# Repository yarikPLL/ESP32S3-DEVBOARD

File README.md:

# ESP32-S3 DevBoard (Recruitment Task)

This project is a custom development board based on the ESP32-S3, created as part of a recruitment task.  
Although the task was intended for candidates, I also completed it myself as a reference and benchmark solution.

## Overview

The board is based on the **ESP32-S3-WROOM-1** module and follows the general idea of standard development boards.

The pinout is **fully compatible with the original ESP32-S3 dev boards**, so it can be used as a drop-in replacement in typical setups.

## Features

- ESP32-S3-WROOM-1 module
- 2x USB Type-C connectors for power, programming, and communication OTG
- USB-to-UART converter based on **CP2102N** with auto-programming circuit
- IMU sensor (BMI270) connected via **I2C**
- 2x user LED indicators (0403) and UART led indicators
- Reset, boot and 2 users buttons
- DIP switch for flexible configuration

## Configuration (DIP Switch)

The board includes a DIP switch that allows:

- Enabling/disabling the USB-to-TTL converter  
- Enabling/disabling the IMU sensor  
- Powering off the ESP32 (useful when using the board purely as a USB-UART converter)

## IMU

An IMU sensor (BMI series) has been added and connected via the I2C interface.  
This allows easy integration of motion sensing features in future projects.

## USB to UART

The board includes a **CP2102N** USB-to-TTL converter with an auto-programming circuit, enabling:

- Firmware flashing
- Serial communication
- Seamless development workflow

## PCB Layout

Below are renders and layout views of the board:

### Layout

### 3D Views

#### Top View

#### Bottom View

#### Isometric Top

#### Isometric Bottom

## Notes

This project was created as part of a recruitment process to evaluate practical hardware design skills, including:

- schematic design
- PCB layout
- manufacturability
- documentation

## License

This project is licensed under the GNU Lesser General Public License v2.1 (LGPL-2.1).

You are free to use, modify, and distribute this project under the terms of this license.

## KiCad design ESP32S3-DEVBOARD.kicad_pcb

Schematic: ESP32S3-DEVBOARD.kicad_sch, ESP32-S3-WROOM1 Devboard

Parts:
C1, C2, C4, C5, C7, C9, C11, C12, C13: 100n; C_0402_1005Metric; MFR Part # CL05B104KO5NNNC; LCSC C1525
C3, C6, C8: 10u_{ 20%}; C_0603_1608Metric; MFR Part # CL10A106MA8NRNC; LCSC C96446
C10, C15, C16: 100n; C_0402_1005Metric; MFR Part # CL05B104KO5NNNC; LCSC C1525; not fitted
C14: 10u_{ 20%}; C_0603_1608Metric; LCSC C96446; not fitted
D1, D3: RED; LED_0402_1005Metric; MFR Part # 16-213SDRC/S530-A3/TR8; LCSC C71911
D2, D4: GREEN; LED_0402_1005Metric; MFR Part # 16-213/GHC-YR1S1/3T; LCSC C74338
J1, J2: PinHeader_1x22_P2.54mm_Vertical; PinHeader_1x22_P2.54mm_Vertical_FLIPPED
J3, J4: G-Switch_GT-USB-7010ASV; USB_C_Receptacle_G-Switch_GT-USB-7010ASV; LCSC C2988369
Q1, Q2: BC817-40,215; LCSC C52801
R1, R5: 0R; R_0402_1005Metric; MFR Part # RC0402FR-070RL; LCSC C106231
R2, R3, R4, R8, R13, R14, R15: 10k; R_0402_1005Metric; MFR Part # RC0402FR-0710KL; LCSC C60490
R6, R7, R16, R17: 5.1k; R_0402_1005Metric; MFR Part # 0402WGF5101TCE; LCSC C25905
R9: 22.1k; R_0402_1005Metric; MFR Part # FRC0402F2212TS; LCSC C2929993
R10: 47.5k; R_0402_1005Metric; MFR Part # 0402WGF4752TCE; LCSC C25896
R11, R12, R20, R21: 1k; R_0402_1005Metric; MFR Part # 0402WGF1001TCE; LCSC C11702
SW1, SW2, SW3, SW4: TS-1088-AR02016; MFR Part # TS-1088-AR02016; LCSC C720477
SW5: SHOU_HAN_1.27-8P_TPPT; SHOU_HAN_1.27-8P_TTPT; MFR Part # 1.27-8P TPPT; LCSC C6386921
U1: AMS1117-3.3; LCSC C6186
U2: ESP32-S3-WROOM-1; LCSC C2913205
U3, U6: USBLC6-2P6; SOT-666; MFR Part # USBLC6-2P6; LCSC C2827693
U4: CP2102N-A02-GQFN28R; LCSC C964632
U5: BMI270; MFR Part # BMI270; LCSC C2836813

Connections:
+3.3V: C1.2, C2.2, C5.1, C6.1, C11.2, C12.1, C13.1, C16.1, J1.1, J1.2, R3.1, R8.1, R11.1, R12.1, R13.1, R14.1, SW5.11, U1.2 (VO), U2.2 (3V3), U4.6 (VDD), U5.5 (VDDIO), U5.8 (VDD)
+5V: C3.1, C4.1, C8.1, C9.1, C10.2, C14.1, C15.1, J1.21, J3.A4 (VBUS), J3.A9 (VBUS), J3.B4 (VBUS), J3.B9 (VBUS), J4.A4 (VBUS), J4.A9 (VBUS), J4.B4 (VBUS), J4.B9 (VBUS), R9.1, U1.3 (VI), U3.5 (VBUS), U6.5 (VBUS)
/CSB_U5: R15.1, SW5.6, U5.12 (CSB)
/DTR: Q2.3 (C), R2.2, U4.28 (~DTR)
/EN: C7.2, J1.3, R1.2, R3.2, SW1.2, SW5.1, U2.3 (EN)
/GPIO0: J2.14, R5.2, SW2.2, U2.27 (IO0)
/GPIO1: J2.4, U2.39 (IO1)
/GPIO2: J2.5, U2.38 (IO2)
/GPIO3: J1.13, U2.15 (IO3)
/GPIO4: J1.4, U2.4 (IO4)
/GPIO5: J1.5, U2.5 (IO5)
/GPIO6: J1.6, U2.6 (IO6)
/GPIO7: J1.7, U2.7 (IO7)
/GPIO8: J1.12, U2.12 (IO8)
/GPIO9: J1.15, U2.17 (IO9)
/GPIO10: J1.16, U2.18 (IO10)
/GPIO11: J1.17, U2.19 (IO11)
/GPIO12: J1.18, U2.20 (IO12)
/GPIO13: J1.19, R20.1, U2.21 (IO13)
/GPIO14: J1.20, R21.1, U2.22 (IO14)
/GPIO15: J1.8, SW3.1, U2.8 (IO15)
/GPIO16: J1.9, SW4.1, U2.9 (IO16)
/GPIO17: J1.10, U2.10 (IO17)
/GPIO18: J1.11, U2.11 (IO18)
/GPIO21: J2.18, SW5.12, U2.23 (IO21)
/GPIO35: J2.13, SW5.15, U2.28 (IO35)
/GPIO36: J2.12, U2.29 (IO36)
/GPIO37: J2.11, U2.30 (IO37)
/GPIO38: J2.10, U2.31 (IO38)
/GPIO39: J2.9, U2.32 (IO39)
/GPIO40: J2.8, U2.33 (IO40)
/GPIO41: J2.7, U2.34 (IO41)
/GPIO42: J2.6, U2.35 (IO42)
/GPIO43: J2.2, SW5.9, U2.37 (TXD0)
/GPIO44: J2.3, SW5.10, U2.36 (RXD0)
/GPIO45: J2.15, U2.26 (IO45)
/GPIO46: J1.14, U2.16 (IO46)
/GPIO47: J2.17, SW5.13, U2.24 (IO47)
/GPIO48: J2.16, SW5.14, U2.25 (IO48)
/INT1: SW5.2, U5.4 (INT1)
/INT2: SW5.5, U5.9 (INT2)
/I^{2}C_SCL: R14.2, SW5.4, U5.13 (SCX)
/I^{2}C_SDA: R13.2, SW5.3, U5.14 (SDX)
/RST: R8.2, U4.9 (~RST)
/RTS: Q1.2 (E), R4.2, U4.24 (~RTS)
/RX_LED: D2.1 (K), U4.18 (~RXT/GPIO.1)
/TX_LED: D1.1 (K), U4.19 (~TXT/GPIO.0)
/U2_RX: SW5.8, U4.25 (RXD)
/U2_TX: SW5.7, U4.26 (TXD)
/U2_VBUS: R9.2, R10.1, U4.8 (VBUS)
/USB0_D+: U3.6 (I/O1), U4.4 (D+)
/USB0_D-: U3.4 (I/O2), U4.5 (D-)
/USB0_T_D+: J3.A6 (D+), J3.B6 (D+), U3.1 (I/O1)
/USB0_T_D-: J3.A7 (D-), J3.B7 (D-), U3.3 (I/O2)
/USB1_D+: J2.19, U2.14 (USB_D+), U6.4 (I/O2)
/USB1_D-: J2.20, U2.13 (USB_D-), U6.6 (I/O1)
/USB1_T_D+: J4.A6 (D+), J4.B6 (D+), U6.3 (I/O2)
/USB1_T_D-: J4.A7 (D-), J4.B7 (D-), U6.1 (I/O1)
/USB_0_CC1: J3.A5 (CC1), R6.1
/USB_0_CC2: J3.B5 (CC2), R7.1
/USB_1_CC1: J4.A5 (CC1), R16.1
/USB_1_CC2: J4.B5 (CC2), R17.1
GND: C1.1, C2.1, C3.2, C4.2, C5.2, C6.2, C7.1, C8.2, C9.2, C10.1, C11.1, C12.2, C13.2, C14.2, C15.2, C16.2, D3.1 (K), D4.1 (K), J1.22, J2.1, J2.21, J2.22, J3.A1 (GND), J3.A12 (GND), J3.B1 (GND), J3.B12 (GND), J3.S1 (SHIELD), J4.A1 (GND), J4.A12 (GND), J4.B1 (GND), J4.B12 (GND), J4.S1 (SHIELD), R6.2, R7.2, R10.2, R15.2, R16.2, R17.2, SW1.1, SW2.1, SW3.2, SW4.2, SW5.16, U1.1 (GND), U2.1 (GND), U2.40 (GND), U2.41 (GND), U3.2 (GND), U4.3 (GND), U4.29 (GND), U5.6 (GNDIO), U5.7 (GND), U6.2 (GND)
unnamed: D1.2 (A), R11.2
unnamed: D2.2 (A), R12.2
unnamed: D3.2 (A), R20.2
unnamed: D4.2 (A), R21.2
unnamed: Q1.1 (B), R2.1
unnamed: Q1.3 (C), R1.1
unnamed: Q2.1 (B), R4.1
unnamed: Q2.2 (E), R5.1

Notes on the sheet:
ESP32-SR-WROOM-1
USB for OTG (ESP)
Auto program Circuit
Connecting TTL to ESP
Connecting IMU to ESP (INTR_{2})
Changing I^{2}C IMU Address
Connecting IMU to ESP (I^{2}C_SCL)
Power LDO 3.3V
USB for TTL
Interactive leds and buttons
Connecting IMU to ESP (INTR_{1})
IMU BMI270 I2C mode
Setting ESP to reset mode
Header pins P2.54mm
USB to TTL
DIP switch for connecting/disconnecting periferia
Connecting IMU to ESP (I^{2}C_SDA)

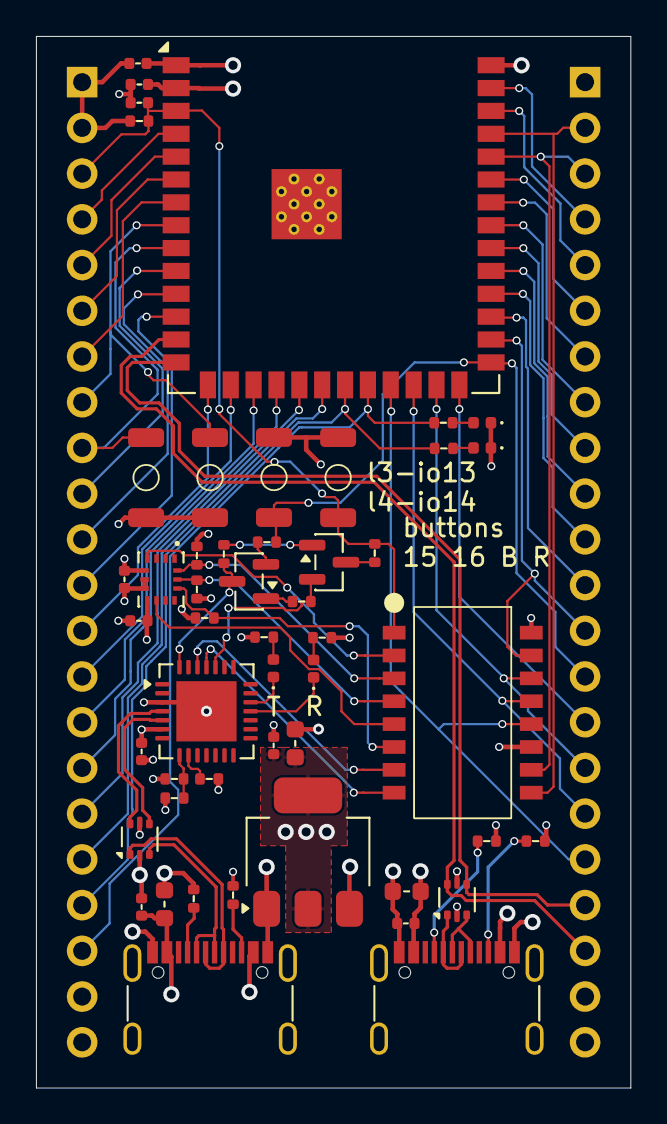
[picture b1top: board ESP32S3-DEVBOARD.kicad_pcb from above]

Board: 4 copper layers, 33.0 x 58.4 mm, 52 parts (0 on the bottom side), 71 nets.

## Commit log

2026-03-20 Created an empty Kicad project
2026-03-21 Created library for USB_C, ESP32, AND CP2102N, starded to draw schematic
2026-03-22 Add goldpin, add LDO
2026-03-22 Add decoupling capacitors
2026-03-23 Add two resisotrs to library
2026-03-24 Add 1k resistors and leds (red and green 0402)
2026-03-24 Add buttons to lib, 0R resistors and LEDS
2026-03-24 Add marks, only imu left
2026-03-24 Finnished a schematic. Rev 1.0.0
2026-03-24 Created pcb project and defined design rules
2026-03-25 Started to rout USB, need swap ports for uart
2026-03-25 Swap usb ports, need to define differential pair
2026-03-26 Defined netclasses for USB
2026-03-26 Routed USB and added uart jumpers
2026-03-26 Removed jumpers, and added dipswitch to schematics
2026-03-26 Changet position of ttl
2026-03-27 Routing usb for ttl
2026-03-27 started to wotk on another laptop
2026-03-28 finish componemt placement
2026-03-28 fixed all errors (edit footprint silkskreens)
2026-03-29 Finnished the board!! :)
2026-03-29 add screenshots
2026-03-29 write readme
2026-03-29 add 3D model
2026-03-29 Add production files
2026-03-29 fixed BOM
2026-03-29 reconfigure fabrication toolkit
